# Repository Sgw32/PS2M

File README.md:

# PS2M Amiga mouse adapter

## You can buy this item here:
https://www.ebay.com/itm/407301065035

** NEW: ATARI VERSION 

Connect your good old laser PS/2 mouse to your Amiga Retro computer with this cheap and reliable adapter(and forget about non-usable old Amiga mouse)

Features: 

1) PS2M firmware with doubled pins for super reliability of PIC MCU

2) Can be edited to work with Atari

3) Plug&play solution

4) Works with all known Amiga author has

Good resolution, high precision.

Truly 100% open source solution, all hw and sw files available. 

Firmware by Denis Sotchenko's PS2M mouse adapter

PCB by mkl211015 (a little bit adopted to modern PCB software by me)

Flashing using TL866 programmer(see source code)

License:

GNU GPL Version 2 (see gpl.txt)

Original information: http://www.mklboards.fi/ps2mhiiri627/

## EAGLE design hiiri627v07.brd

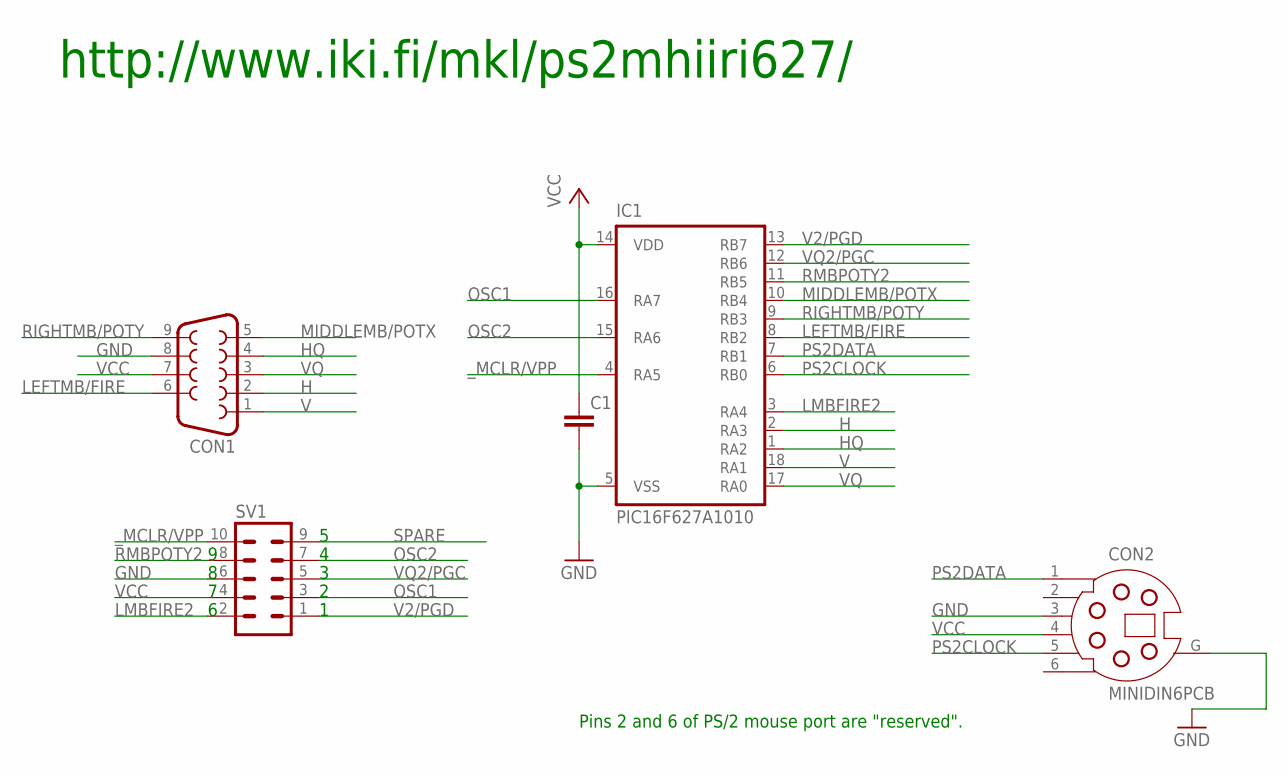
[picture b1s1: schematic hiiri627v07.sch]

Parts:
C1: C-EUC0805K; C0805K
CON1: F09D
CON2: MINIDIN6PCB
IC1: PIC16F627A1010; SO18-10101020
SV1: ML10

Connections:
GND: C1.2, CON1.8, CON2.3, CON2.G, IC1.5 (VSS), SV1.6
H: CON1.2, IC1.2 (RA3)
HQ: CON1.4, IC1.1 (RA2)
LEFTMB/FIRE: CON1.6, IC1.8 (RB2)
LMBFIRE2: IC1.3 (RA4), SV1.2
MIDDLEMB/POTX: CON1.5, IC1.10 (RB4)
OSC1: IC1.16 (RA7), SV1.3
OSC2: IC1.15 (RA6), SV1.7
PS2CLOCK: CON2.5, IC1.6 (RB0)
PS2DATA: CON2.1, IC1.7 (RB1)
RIGHTMB/POTY: CON1.9, IC1.9 (RB3)
RMBPOTY2: IC1.11 (RB5), SV1.8
SPARE: SV1.9
V: CON1.1, IC1.18 (RA1)
V2/PGD: IC1.13 (RB7), SV1.1
VCC: C1.1, CON1.7, CON2.4, IC1.14 (VDD), SV1.4
VQ: CON1.3, IC1.17 (RA0)
VQ2/PGC: IC1.12 (RB6), SV1.5
_MCLR/VPP: IC1.4 (RA5), SV1.10

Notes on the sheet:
Pins 2 and 6 of PS/2 mouse port are "reserved".
http://www.iki.fi/mkl/ps2mhiiri627/

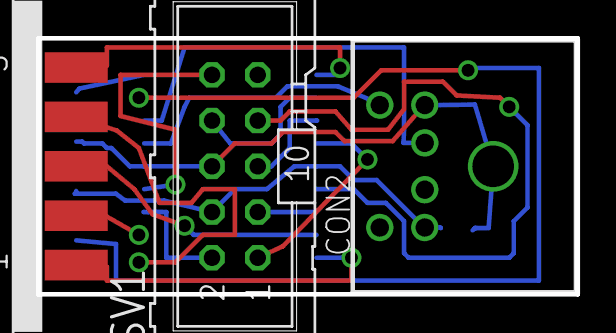
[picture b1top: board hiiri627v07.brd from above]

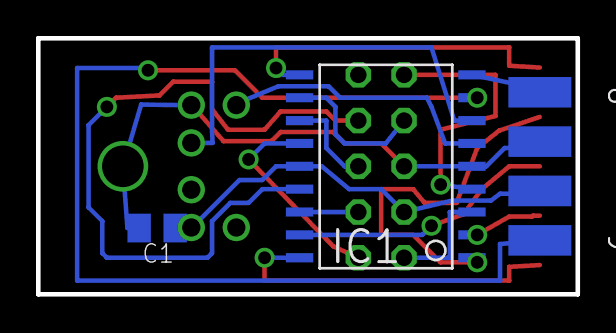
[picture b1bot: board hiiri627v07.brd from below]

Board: 2 copper layers, 30.0 x 14.2 mm, 5 parts (2 on the bottom side), 18 nets.

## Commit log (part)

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2021-01-03 PS2M initial commit
2022-02-11 Big one board + PS2M for Atari + PS2M for tssop pic
2022-02-11 atari for README.md
